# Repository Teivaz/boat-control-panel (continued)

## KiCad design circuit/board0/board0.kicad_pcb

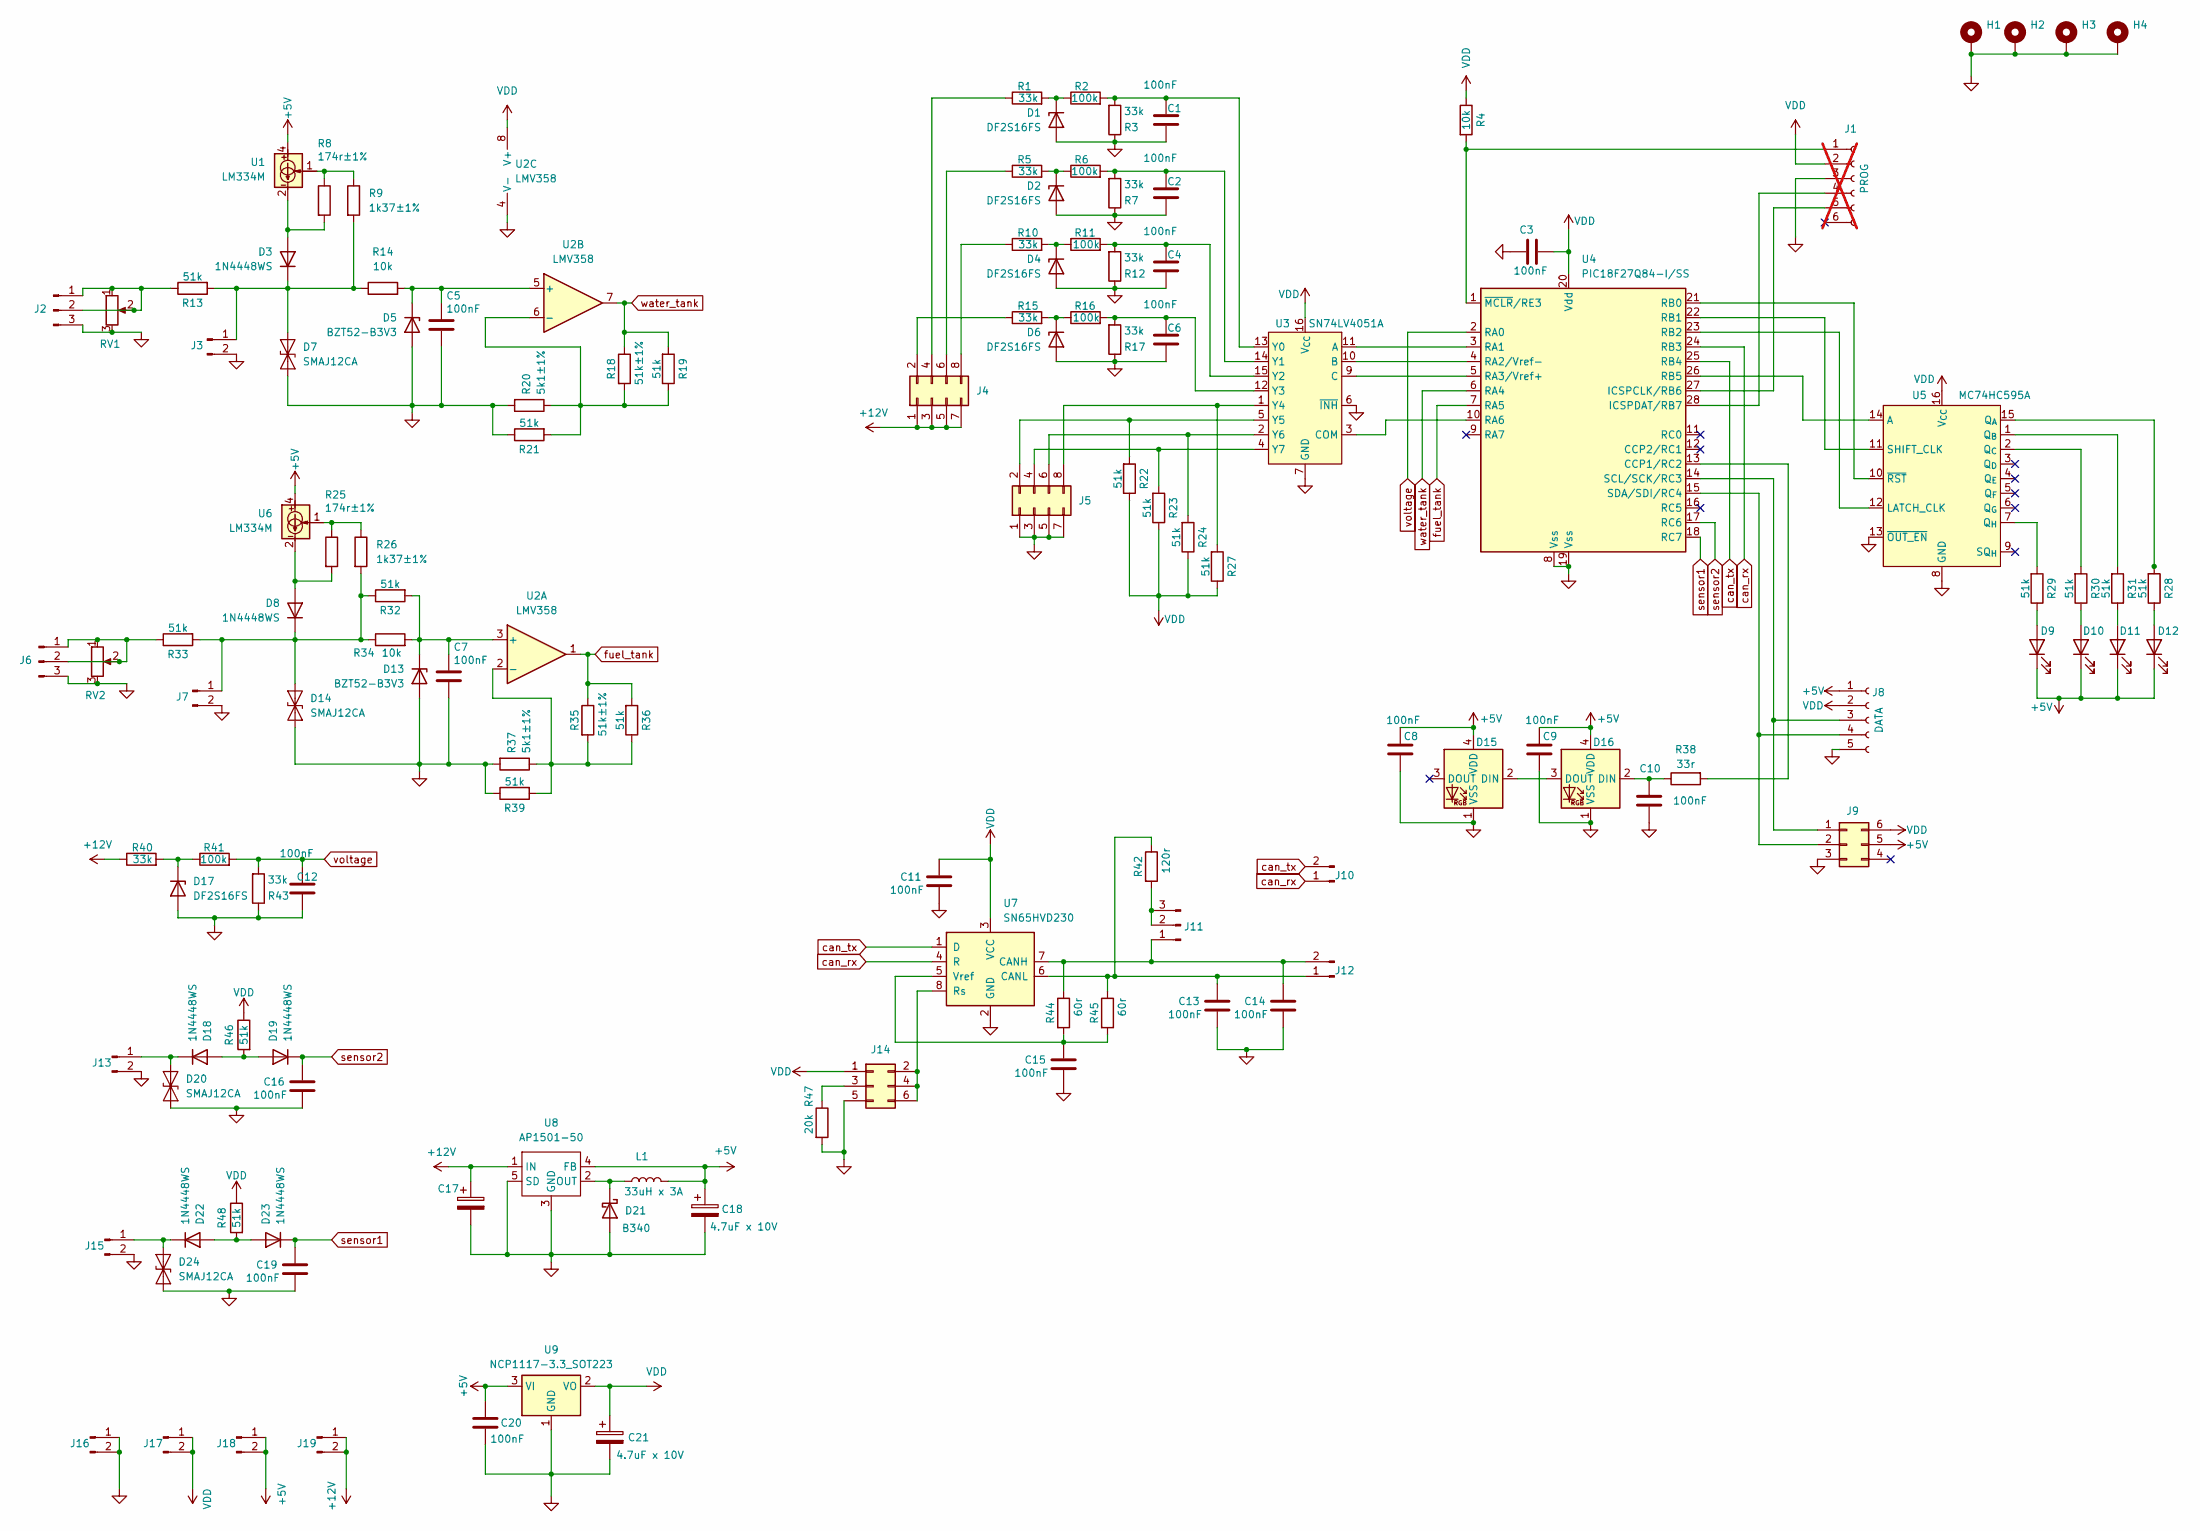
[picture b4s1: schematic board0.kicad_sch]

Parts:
C1, C2, C3, C4, C5, C6, C7, C8, C9, C10, C11, C12, C13, C14, C15, C16, C19, C20: 100nF; C_0805_2012Metric_Pad1.18x1.45mm_HandSolder
C17: 4.7uFx50V; C_Elec_5x5.4
C18, C21: 4.7uF x 10V; CP_EIA-3216-10_Kemet-I_HandSolder
D1, D2, D4, D6, D17: DF2S16FS; D_SOD-923
D3, D8, D18, D19, D22, D23: 1N4448WS; D_SOD-323_HandSoldering
D5, D13: BZT52-B3V3; D_SOD-123
D7, D14, D20, D24: SMAJ12CA; D_SMA
D9, D10, D11, D12: LED; LED_D3.0mm
D15, D16: LiteOn_LTST-E563C; LED_LiteOn_LTST-E563C_PLCC4_5.0x5.0mm_P3.2mm
D21: B340; D_SMC
H1, H2, H3, H4: MountingHole_Pad; MountingHole_3.2mm_M3_Pad_Via
J1: PinHeader_1x06_P2.54mm_Vertical; not fitted
J2, J6, J11: Conn_01x03_Pin; PinHeader_1x03_P2.54mm_Vertical
J3, J7, J10, J12, J13, J15, J16, J17, J18, J19: Conn_01x02_Pin; PinHeader_1x02_P2.54mm_Vertical
J4, J5: Conn_02x08_Odd_Even; PinHeader_2x04_P2.54mm_Vertical
J8: Molex_Pico-Lock_504050-0591_1x05-1MP_P1.50mm_Horizontal
J9: Conn_02x03_Counter_Clockwise; Con-Amphenol-76385-303LF
J14: Conn_02x08_Odd_Even; PinHeader_2x03_P2.54mm_Vertical
L1: 33uH x 3A; L_Abracon_AMDLA1004S-330MT
R1, R3, R5, R7, R10, R12, R15, R17, R40, R43: 33k; R_0805_2012Metric_Pad1.20x1.40mm_HandSolder
R2, R6, R11, R16, R41: 100k; R_0805_2012Metric_Pad1.20x1.40mm_HandSolder
R4, R14, R34: 10k; R_0805_2012Metric_Pad1.20x1.40mm_HandSolder
R8, R25: 174r±1%; R_0805_2012Metric_Pad1.20x1.40mm_HandSolder
R9, R26: 1k37±1%; R_0805_2012Metric_Pad1.20x1.40mm_HandSolder
R13, R19, R21, R22, R23, R24, R27, R28, R29, R30, R31, R32, R33, R36, R39: 51k; R_Axial_DIN0207_L6.3mm_D2.5mm_P10.16mm_Horizontal
R18, R35: 51k±1%; R_0805_2012Metric_Pad1.20x1.40mm_HandSolder
R20, R37: 5k1±1%; R_0603_1608Metric_Pad0.98x0.95mm_HandSolder
R38: 33r; R_0805_2012Metric_Pad1.20x1.40mm_HandSolder
R42: 120r; R_0805_2012Metric_Pad1.20x1.40mm_HandSolder
R44, R45: 60r; R_0805_2012Metric_Pad1.20x1.40mm_HandSolder
R46, R48: 51k; R_0805_2012Metric_Pad1.20x1.40mm_HandSolder
R47: 20k; R_0805_2012Metric_Pad1.20x1.40mm_HandSolder
RV1, RV2: R_Potentiometer; Pot-linear-PDV
U1, U6: LM334M; SOIC-8_3.9x4.9mm_P1.27mm
U2: LMV358; SOIC-8_3.9x4.9mm_P1.27mm
U3: SN74LV4051A; SOIC-16_3.9x9.9mm_P1.27mm
U4: PIC18F27Q84-I/SS; SSOP-28-5.3mm
U5: MC74HC595A; SOIC-16_3.9x9.9mm_P1.27mm
U7: SN65HVD230; SOIC-8_3.9x4.9mm_P1.27mm
U8: AP1501-50; TO-263-5_TabPin3
U9: NCP1117-3.3_SOT223; SOT-223-3_TabPin2

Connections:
+5V: C8.1, C9.1, C18.1, C20.1, D9.1 (K), D10.1 (K), D11.1 (K), D12.1 (K), D15.4 (VDD), D16.4 (VDD), J8.1, J9.5, J18.1, J18.2, L1.2, U1.4, U6.4, U8.4 (FB), U9.3 (VI)
+12V: C17.1, J4.1, J4.3, J4.5, J4.7, J19.1, J19.2, R40.1, U8.1 (IN)
GND: C1.1, C2.1, C3.2, C4.1, C5.2, C6.1, C7.2, C8.2, C9.2, C10.1, C11.2, C12.1, C13.2, C14.2, C15.2, C16.2, C17.2, C18.2, C19.2, C20.2, C21.2, D1.2 (A), D2.2 (A), D4.2 (A), D5.2 (A), D6.2 (A), D7.1 (A1), D13.2 (A), D14.1 (A1), D15.1 (VSS), D16.1 (VSS), D17.2 (A), D20.1 (A1), D21.2 (A), D24.1 (A1), H1.1, H2.1, H3.1, H4.1, J1.3, J2.3, J3.2, J5.1, J5.3, J5.5, J5.7, J6.3, J7.2, J8.5, J9.3, J13.2, J14.5, J15.2, J16.1, J16.2, R3.1, R7.1, R12.1, R17.1, R20.2, R21.1, R37.2, R39.1, R43.1, R47.2, RV1.3, RV1.3a (3), RV1.3b (3), RV1.3c (3), RV1.3d (3), RV1.3e (3), RV2.3, RV2.3a (3), RV2.3b (3), RV2.3c (3), RV2.3d (3), RV2.3e (3), U2.4 (V-), U3.6 (~INH), U3.7 (GND), U3.8 (GND), U4.8 (Vss), U4.19 (Vss), U5.8 (GND), U5.13 (~OUT_EN), U7.2 (GND), U8.3 (GND), U8.5 (SD), U9.1 (GND)
unnamed: D1.1 (K), R1.2, R2.1
unnamed: D2.1 (K), R5.2, R6.1
unnamed: D3.2 (A), R8.2, U1.2, U1.3, U1.6, U1.7
unnamed: D3.1 (K), D7.2 (A2), J3.1, R9.2, R13.2, R14.1
unnamed: D4.1 (K), R10.2, R11.1
unnamed: C5.1, D5.1 (K), R14.2, U2.5 (+)
unnamed: D6.1 (K), R15.2, R16.1
unnamed: D8.2 (A), R25.2, U6.2, U6.3, U6.6, U6.7
unnamed: D9.2 (A), R29.1
unnamed: D10.2 (A), R30.1
unnamed: D11.2 (A), R31.1
unnamed: D12.2 (A), R28.1
unnamed: C7.1, D13.1 (K), R32.2, R34.2, U2.3 (+)
unnamed: D8.1 (K), D14.2 (A2), J7.1, R26.2, R32.1, R33.2, R34.1
unnamed: D15.2 (DIN), D16.3 (DOUT)
unnamed: C10.2, D16.2 (DIN), R38.1
unnamed: D17.1 (K), R40.2, R41.1
unnamed: D18.2 (A), D19.2 (A), R46.2
unnamed: D18.1 (K), D20.2 (A2), J13.1
unnamed: D21.1 (K), L1.1, U8.2 (OUT)
unnamed: D22.2 (A), D23.2 (A), R48.2
unnamed: D22.1 (K), D24.2 (A2), J15.1
unnamed: J1.1, R4.2, U4.1 (~MCLR/RE3)
unnamed: J1.4, U4.28 (ICSPDAT/RB7)
unnamed: J1.5, U4.27 (ICSPCLK/RB6)
unnamed: J2.1, J2.2, R13.1, RV1.1, RV1.2
unnamed: J4.2, R15.1
unnamed: J4.4, R1.1
unnamed: J4.6, R5.1
unnamed: J4.8, R10.1
unnamed: J5.2, R22.2, U3.5 (Y5)
unnamed: J5.4, R23.2, U3.4 (Y7)
unnamed: J5.6, R24.2, U3.2 (Y6)
unnamed: J5.8, R27.2, U3.1 (Y4)
unnamed: J6.1, J6.2, R33.1, RV2.1, RV2.2
unnamed: J8.3, J9.1, U4.14 (SCL/SCK/RC3)
unnamed: J8.4, J9.2, U4.15 (SDA/SDI/RC4)
unnamed: C14.1, J11.1, J12.2, R44.1, U7.7 (CANH)
unnamed: J11.2, J11.3, R42.2
unnamed: C13.1, J12.1, R42.1, R45.1, U7.6 (CANL)
unnamed: J14.2, J14.4, J14.6, U7.8 (Rs)
unnamed: J14.3, R47.1
unnamed: R8.1, R9.1, U1.1
unnamed: R25.1, R26.1, U6.1
unnamed: R35.2, R36.1, R37.1, R39.2, U2.2 (-)
unnamed: R18.2, R19.1, R20.1, R21.2, U2.6 (-)
unnamed: U3.11 (A), U4.3 (RA1)
unnamed: U3.10 (B), U4.4 (RA2/Vref-)
unnamed: U3.9 (C), U4.5 (RA3/Vref+)
unnamed: U3.3 (COM), U4.10 (RA6)
unnamed: C1.2, R2.2, R3.2, U3.13 (Y0)
unnamed: C2.2, R6.2, R7.2, U3.14 (Y1)
unnamed: C4.2, R11.2, R12.2, U3.15 (Y2)
unnamed: C6.2, R16.2, R17.2, U3.12 (Y3)
unnamed: R38.2, U4.13 (CCP1/RC2)
unnamed: U4.21 (RB0), U5.10 (~RST)
unnamed: U4.22 (RB1), U5.11 (SHIFT_CLK)
unnamed: U4.23 (RB2), U5.12 (LATCH_CLK)
unnamed: U4.26 (RB5), U5.14 (A)
unnamed: R28.2, U5.15 (Q_{A})
unnamed: R31.2, U5.1 (Q_{B})
unnamed: R30.2, U5.2 (Q_{C})
unnamed: R29.2, U5.7 (Q_{H})
unnamed: C15.1, R44.2, R45.2, U7.5 (Vref)
VDD: C3.1, C11.1, C21.1, J1.2, J8.2, J9.6, J14.1, J17.1, J17.2, R4.1, R22.1, R23.1, R24.1, R27.1, R46.1, R48.1, U2.8 (V+), U3.16 (V_{CC}), U4.20 (Vdd), U5.16 (V_{CC}), U7.3 (VCC), U9.2 (VO)
can_rx: J10.1, U4.24 (RB3), U7.4 (R)
can_tx: J10.2, U4.25 (RB4), U7.1 (D)
fuel_tank: R35.1, R36.2, U2.1, U4.7 (RA5)
sensor1: C19.1, D23.1 (K), U4.18 (RC7)
sensor2: C16.1, D19.1 (K), U4.17 (RC6)
voltage: C12.2, R41.2, R43.2, U4.2 (RA0)
water_tank: R18.1, R19.2, U2.7, U4.6 (RA4)

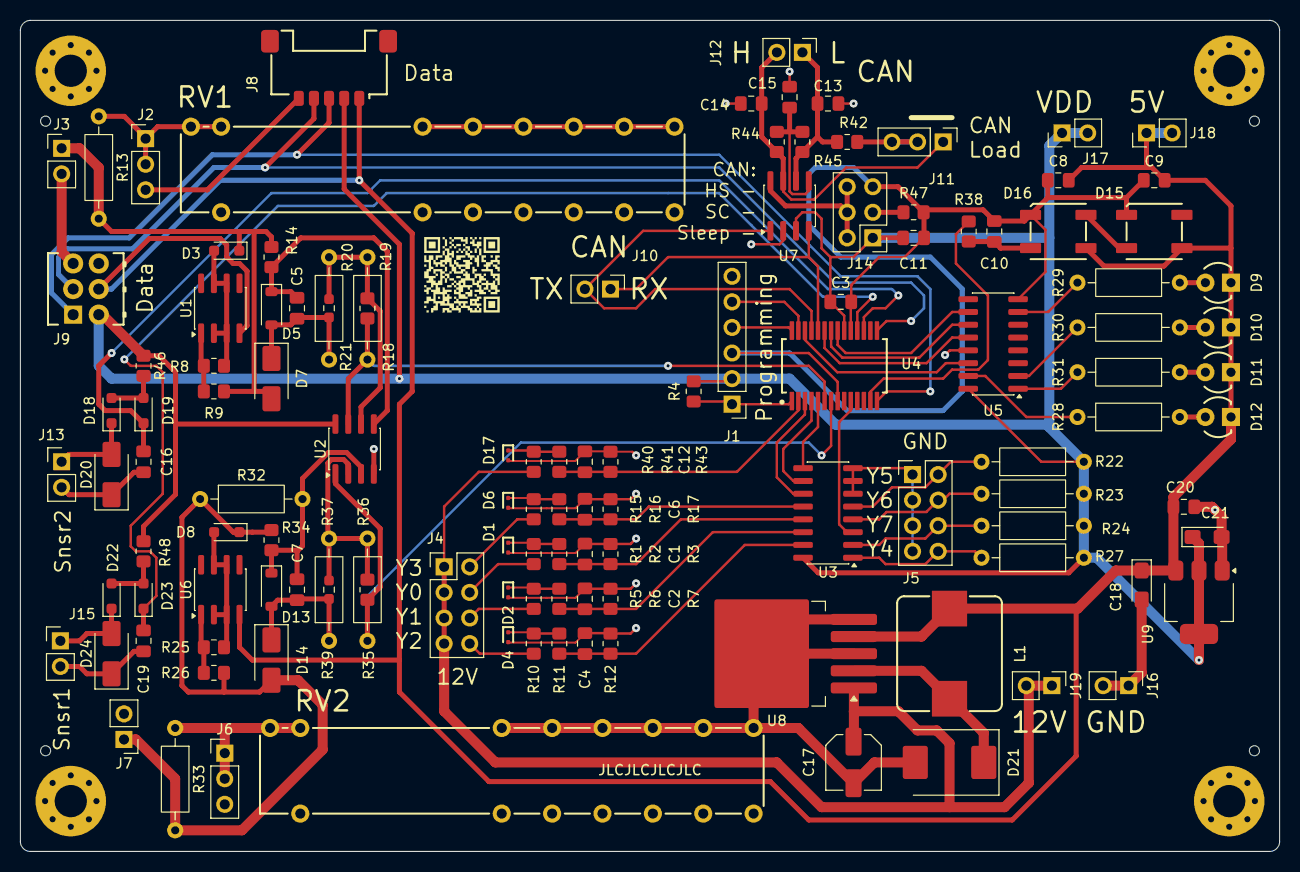
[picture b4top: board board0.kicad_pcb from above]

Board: 2 copper layers, 125.0 x 82.5 mm, 128 parts (0 on the bottom side), 75 nets.

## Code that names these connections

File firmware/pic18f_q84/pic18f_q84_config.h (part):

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 *              0 = IVTLOCKED can be set and cleared repeatedly
 *
 *    Bit 5   - MCLRE    Master Clear Enable
 *              1 = RE3 pin functions as MCLR (active-low reset input)
 *              0 = RE3 pin functions as digital input (MCLR internally tied)
 *
 *    Bit 4   - Reserved (read as 1)
 *
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/* -- Bit masks ------------------------------------------------------------ */
#define CONFIG3_MVECEN (1u << CONFIG3_MVECEN_POS)   /**< 0x80 - 1=multi-vector interrupts  */
#define CONFIG3_IVT1WAY (1u << CONFIG3_IVT1WAY_POS) /**< 0x40 - 1=IVT one-way lock        */
#define CONFIG3_MCLRE (1u << CONFIG3_MCLRE_POS)     /**< 0x20 - 1=MCLR enabled on RE3     */
#define CONFIG3_BOREN_MASK 0x0Cu                    /**< BOR enable field [3:2]           */
#define CONFIG3_LPBOREN (1u << CONFIG3_LPBOREN_POS) /**< 0x02 - 1=low-power BOR enabled    */
#define CONFIG3_PPS1WAY (1u << CONFIG3_PPS1WAY_POS) /**< 0x01 - 1=PPS one-way lock         */
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 *              0 = Background debugger disabled
 *
 *    Bit 2   - LVP      Low-Voltage Programming Enable
 *              1 = Low-voltage programming enabled (PGM pin is LVP entry)
 *              0 = HV on MCLR required for programming
 *
 *    Bit 1:0 - BORV[1:0]  Brown-out Reset Voltage Selection
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#define CONFIG4_STVREN (1u << CONFIG4_STVREN_POS) /**< 0x20 - 1=stack over/underflow reset*/
#define CONFIG4_XINST (1u << CONFIG4_XINST_POS)   /**< 0x10 - 1=extended instruction set  */
#define CONFIG4_DEBUG (1u << CONFIG4_DEBUG_POS)   /**< 0x08 - 1=debug mode enabled        */
#define CONFIG4_LVP (1u << CONFIG4_LVP_POS)       /**< 0x04 - 1=low-voltage programming   */
#define CONFIG4_BORV_MASK 0x03u                   /**< BOR voltage field [1:0]          */

/* -- BORV field values ---------------------------------------------------- */
#define CONFIG4_BORV_HIGH 0x00u   /**< Highest BOR trip point (~2.85V)  */
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#define CONFIG10_CP (1u << CONFIG10_CP_POS)       /**< 0x01 - 1=code NOT protected   */

/* -- BOOTPINSEL field values ---------------------------------------------- */
#define CONFIG10_BOOTPINSEL_RA4 (0x00u << CONFIG10_BOOTPINSEL_POS) /**< RA4 as boot pin (default) */
#define CONFIG10_BOOTPINSEL_RA5 (0x01u << CONFIG10_BOOTPINSEL_POS) /**< RA5 as boot pin           */
#define CONFIG10_BOOTPINSEL_RA6 (0x02u << CONFIG10_BOOTPINSEL_POS) /**< RA6 as boot pin           */
#define CONFIG10_BOOTPINSEL_RA7 (0x03u << CONFIG10_BOOTPINSEL_POS) /**< RA7 as boot pin           */

/* ============================================================================
 *  CONFIG11 - Boot / Code Security
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
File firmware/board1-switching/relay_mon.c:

#include "relay_mon.h"

#include <xc.h>

/* Two SN74LV4051A muxes addressed in parallel (A/B/C shared). Each mux
 * routes one of its 8 inputs to its COM pin: mux 0 -> RA3, mux 1 -> RA4.
 * nINH is tied to GND, so the muxes are always enabled.
 *
 * Readme pinout:
 *   RB3 A
 *   RB4 B
 *   RB5 C
 *   RA3 0COM
 *   RA4 1COM
 *
 * The wire-bit-position to (mux, mux-address) layout is embedded in the
 * two 8-element lookup tables below — one per mux — so a single pass
 * through the 8 addresses fills all 16 wire bits. */

#define SEL_A LATBbits.LATB3
#define SEL_B LATBbits.LATB4
#define SEL_C LATBbits.LATB5
#define COM_0 PORTAbits.RA3
#define COM_1 PORTAbits.RA4

/* mux0_to_wire[addr] = the wire bit that mux 0 channel `addr` monitors. */
static const uint8_t mux0_to_wire[8] = {
    6, /* addr 0 -> anchor_light     (wire 6) */
    7, /* addr 1 -> tricolor_light   (wire 7) */
    9, /* addr 2 -> fresh_water_pump (wire 9) */
    5, /* addr 3 -> steaming_light   (wire 5) */
    4, /* addr 4 -> stern_light      (wire 4) */
    0, /* addr 5 -> main             (wire 0) */
    3, /* addr 6 -> bow_light        (wire 3) */
    2, /* addr 7 -> autopilot        (wire 2) */
};

/* mux1_to_wire[addr] = the wire bit that mux 1 channel `addr` monitors. */
static const uint8_t mux1_to_wire[8] = {
    13, /* addr 0 -> usb           (wire 13) */
    12, /* addr 1 -> cabin_lights  (wire 12) */
    1,  /* addr 2 -> instruments   (wire 1)  */
    11, /* addr 3 -> deck_lights   (wire 11) */
    15, /* addr 4 -> aux2          (wire 15) */
    10, /* addr 5 -> fridge        (wire 10) */
    14, /* addr 6 -> aux1          (wire 14) */
    8,  /* addr 7 -> inverter      (wire 8)  */
};

void relay_mon_init(void) {
    /* Select pins RB3/RB4/RB5: digital outputs. */
    ANSELBbits.ANSELB3 = 0;
    ANSELBbits.ANSELB4 = 0;
    ANSELBbits.ANSELB5 = 0;
    LATBbits.LATB3 = 0;
    LATBbits.LATB4 = 0;
    LATBbits.LATB5 = 0;
    TRISBbits.TRISB3 = 0;
    TRISBbits.TRISB4 = 0;
    TRISBbits.TRISB5 = 0;

    /* COM inputs RA3/RA4: digital inputs. Even though the SN74LV4051A is
     * analog-capable, the upstream signal is a logic-level relay-power
     * indicator so reading them as digital is sufficient. */
    ANSELAbits.ANSELA3 = 0;
    ANSELAbits.ANSELA4 = 0;
    TRISAbits.TRISA3 = 1;
    TRISAbits.TRISA4 = 1;
}

uint16_t relay_mon_read(void) {
    uint16_t result = 0;
    for (uint8_t addr = 0; addr < 8; addr++) {
        SEL_A = (addr >> 0) & 1u;
        SEL_B = (addr >> 1) & 1u;
        SEL_C = (addr >> 2) & 1u;
        /* SN74LV4051A typical enable/transition time < 14 ns at 3.3 V.
         * A single NOP at 64 MHz (~15.6 ns) is just enough for it.*/
        __asm("NOP");
        if (COM_0) {
            result |= (uint16_t)(1u << mux0_to_wire[addr]);
        }
        if (COM_1) {
            result |= (uint16_t)(1u << mux1_to_wire[addr]);
        }
    }
    return result;
}

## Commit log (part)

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2026-02-09 Rearranged project
2026-02-10 Finished switching board
2026-02-10 Finished schematic for main board
2026-02-10 Changed signal connector to 6 pos
2026-02-11 Prepared buttons board
2026-02-11 Changed footprint of programming connector to smd 2mm
2026-02-11 Changed jumper connector to 2mm SMD
2026-02-11 Routed bilge pump through IC Added shore power and AC power signals
2026-02-12 Adjusted switching board connection order
2026-02-12 Added 3d models
2026-02-12 Added 3d model for terminal block
2026-02-12 Updated footprints
2026-02-17 Switched to 3.3V Added ESD protection Added display
2026-02-18 Added ESD and footprints
2026-02-18 Updated buttons layout
2026-02-19 Added ESD protection for other inputs Updated footprints
2026-02-19 Routed most of board 1
2026-02-22 Finished initail preparation of board 2
2026-02-23 Finished initail preparation of board 1
2026-02-23 Increased width of the board by 2mm to simplify manufacturing
2026-02-24 Fixed footprints and clearances
2026-02-25 Rerouted thinner traces
2026-02-25 Min thickness 0.2
2026-02-26 Moved op amps to board 1
2026-02-28 Fixed signal measurment
2026-02-28 Added decoupling capacitors
2026-02-28 Added missing 3d models
2026-03-01 Changed button Added led pipes Removed diodes
2026-03-02 Added prototype board
2026-03-02 Added stencil index hole
2026-03-02 fabrication order 1
2026-03-03 Added new ledpipe
2026-03-06 Routed board 3
2026-03-08 Routed boards 1 and 3
2026-04-06 Added pull up for I2C Refined the analog scheme Added DNP backup elements Added level shift for LEDs
2026-04-06 Turned power sybmols
2026-04-07 Fixed display layout
2026-04-07 Fixed main board layout
2026-04-08 Added mounting holes for board 1
2026-04-09 Added vias to main board
2026-04-09 Prepared export
2026-04-09 Fixed warnings for manufacturing
2026-04-09 order/02
2026-04-10 Removed solder paste from mounting holes for screen
2026-04-14 Added user marking on PCB for screen
2026-04-14 Created build scripts Added board2 firmware
2026-04-14 Added protocol draft
2026-04-14 Added libcomm draft
2026-04-15 Update protocol
2026-04-15 Fixed compilation errors
2026-04-16 Refined protocol
2026-04-16 Fixed PCB resistor reference
2026-04-16 Added claude.md
2026-04-16 Added tasks
2026-04-17 Added button effect controller
2026-04-18 Fixed warnings Fixed timer interval
2026-04-18 Added oval mounting hole Fixed button indexing
2026-04-18 Added led effects
2026-04-18 Updated config
2026-04-18 Implemented i2c communications
2026-04-18 Added default config
2026-04-19 Tweaked task
2026-04-19 Added readme for the new boards
2026-04-19 Generated firmware for board 3
2026-04-19 Generated code for board1 switching
2026-04-19 Formatted code
2026-04-19 Not allowing short if statements
2026-04-19 Updated ignore files
2026-04-19 Added liquid sloshing compensation
2026-04-19 Added connection diagram for the panel
2026-04-19 Added u8g2 library
2026-04-20 Implemented more items to the menu
2026-04-20 Cleaned up code, unified style
2026-04-20 Updated connection diagram
2026-04-21 Fixed minor issues in Board 1
2026-04-21 Simplified interrupt handling
2026-04-24 raw claude
2026-04-24 Fixed minor issues
2026-04-24 Fixed I2C timing on main board Moved control buttons to left panel Button message now sends more data in fewer bytes
2026-04-24 Fixed I2C timing Added recovery from RTC error
2026-04-25 minor tweaks to board 2 pcb
2026-04-25 refactored i2c
2026-04-26 WIP protocol implementation
2026-04-26 Moved i2c to central library
2026-04-26 Moved board3 to new api
2026-04-26 compiling as static library
2026-04-27 WIP reimplementing i2c
2026-04-28 Reimplemented I2C
2026-04-29 Fixed bugs
2026-04-30 Enabled interrupts Trying to fix dependency change deteciton while building
2026-04-30 Switching modes between client and host
2026-04-30 Removed redundant mode changes
2026-04-30 fixed count
2026-05-01 Fixed race condition
2026-05-01 DMA TX channel is now armed after start
2026-05-01 Send last byte as NACK when transmitting
2026-05-01 Added result to callback
2026-05-01 Extended time for bus free
2026-05-01 Added missing event handlers Moved button code to use i2c from libcomm
2026-05-01 Fixed warnings in makefiles
2026-05-01 no NACK at the end of host reads
2026-05-01 Attempted fix of byte offset upon first transmit
2026-05-01 fix of byte offset upon first transmit
2026-05-01 Added nack at the end of reading
2026-05-02 Migrated board1 to libcomm
2026-05-02 clearing SIRQEN
2026-05-03 Fixed ADC for board 1
2026-05-03 Another refactor of i2c
2026-05-08 Fixed I2C some state transitions
2026-05-09 Fixed error
2026-05-09 put back the dma priority
2026-05-09 removed tmp code
2026-05-10 Added sync callcaback function
2026-05-10 Removed temp code
2026-05-10 Attempted fix for a missing fir read bit
2026-05-10 reverted wrong code disarming DMA with event
2026-05-10 Added i2c logger
2026-05-10 Added missing import
2026-05-10 Fixed reboot loop error
2026-05-10 Reduced font size
2026-05-10 Fixed event logging
2026-05-10 Added font
2026-05-10 Implemented CRC check
2026-05-10 Updated board state on/off
2026-05-17 Addedd inspector CLI
2026-05-17 Added calibration of ADC
2026-05-17 Updated CRC to be non-null on null message
2026-05-18 Added error display when floats are not connected
2026-05-18 Added CP2112 support to inspector
2026-05-18 Moved ADC to low priority on switching board No success rate is 99% on 100kHz
2026-05-18 Low priority interrupts for remaining boards
2026-05-18 Fixed relay indexing
2026-05-18 Enabled fast mode for i2c
2026-05-18 Fixed formatting issue in inspector
2026-05-18 Fixed clock hogging on reading
2026-05-18 Fixed i2c communication errors
2026-05-19 Updated display
2026-05-19 Updated task comments
2026-05-20 WIP refactor board 3
2026-05-20 WIP refactor board 3 part 2
2026-05-20 WIP refactor board 3 part 3
2026-05-20 Trying to fix total mess
2026-05-22 Added brightness config
2026-05-22 WIP refactor messaging
2026-05-22 Added config calibration menu
2026-05-22 CRC checks and fix
2026-05-24 Cleaned up controller
2026-05-24 Adjusted timing
2026-05-25 Displaying calibration values
2026-05-25 Button effect shows in config mode
2026-05-25 Added client tx buffer clearing
2026-05-25 Added error logging
2026-05-25 Changed signature of void comm_on_config_read_response to pass result Changed LED_DEFAULT_BRIGHTNESS to 0x10 changed INDICATOR_DEFAULT_BRIGHTNESS to 0x10 Moved irrelevant function from controller to 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
2026-05-25 Updated signature of comm_on_button_state_read_response and remaining read response functions to include result
2026-05-25 Fixed some cases of reading
